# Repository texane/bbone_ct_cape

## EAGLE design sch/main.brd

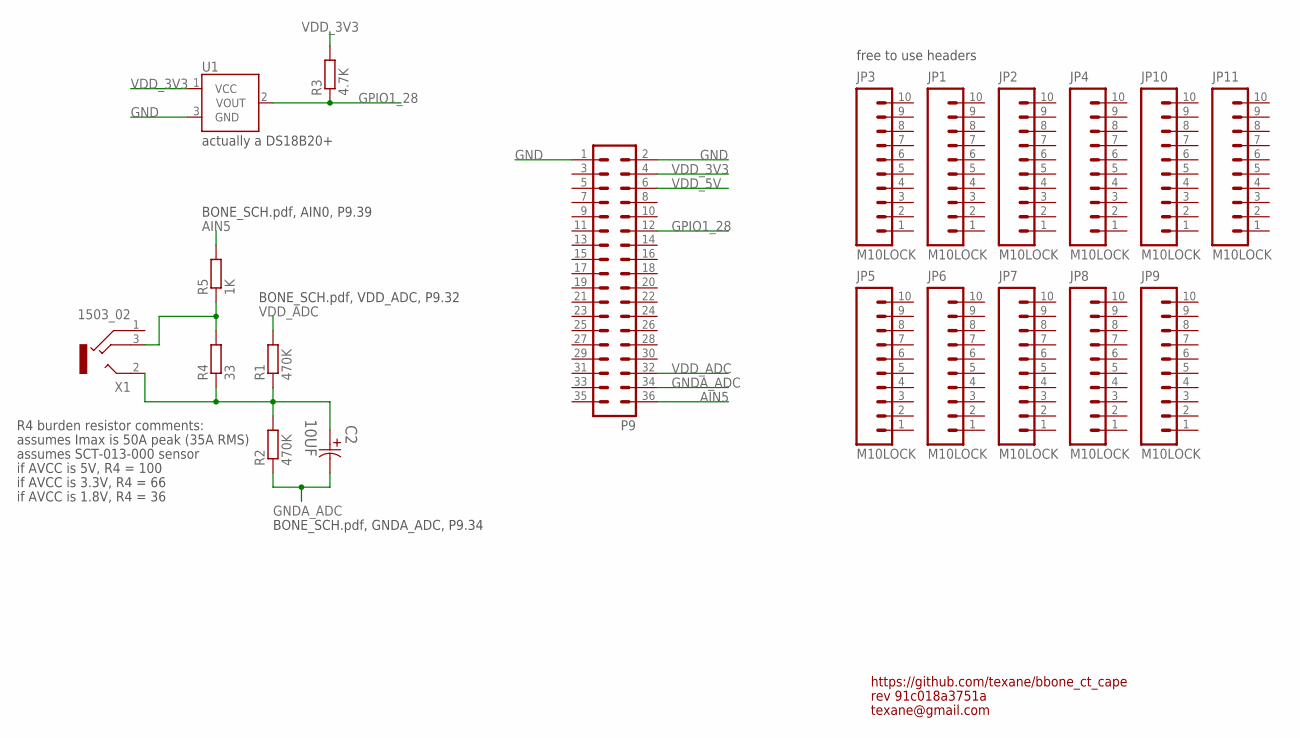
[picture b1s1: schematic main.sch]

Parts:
C2: 10UF; CAPAE530X610N
JP1, JP2, JP3, JP4, JP5, JP6, JP7, JP8, JP9, JP10, JP11: M10LOCK; 1X10_LOCK
P9: MA18-2
R1, R2: 470K; M1206
R3: 4.7K; M1206
R4: 33; M1206
R5: 1K; M1206
U1: TMP36TO-92-KIT; TO-92-KIT
X1: 1503_02

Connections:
AIN5: P9.36, R5.2
GND: P9.1, P9.2, U1.3 (GND)
GNDA_ADC: C2.2, P9.34, R2.1
GPIO1_28: P9.12, R3.1, U1.2 (VOUT)
unnamed: C2.1, R1.1, R2.2, R4.1, X1.2
unnamed: R4.2, R5.1, X1.3
VDD_3V3: P9.4, R3.2, U1.1 (VCC)
VDD_5V: P9.6
VDD_ADC: P9.32, R1.2

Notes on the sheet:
R4 burden resistor comments:
if AVCC is 5V, R4 = 100
if AVCC is 3.3V, R4 = 66
if AVCC is 1.8V, R4 = 36
assumes Imax is 50A peak (35A RMS)
assumes SCT-013-000 sensor
BONE_SCH.pdf, VDD_ADC, P9.32
BONE_SCH.pdf, GNDA_ADC, P9.34
BONE_SCH.pdf, AIN0, P9.39
actually a DS18B20+
free to use headers
texane@gmail.com
rev 91c018a3751a
https://github.com/texane/bbone_ct_cape

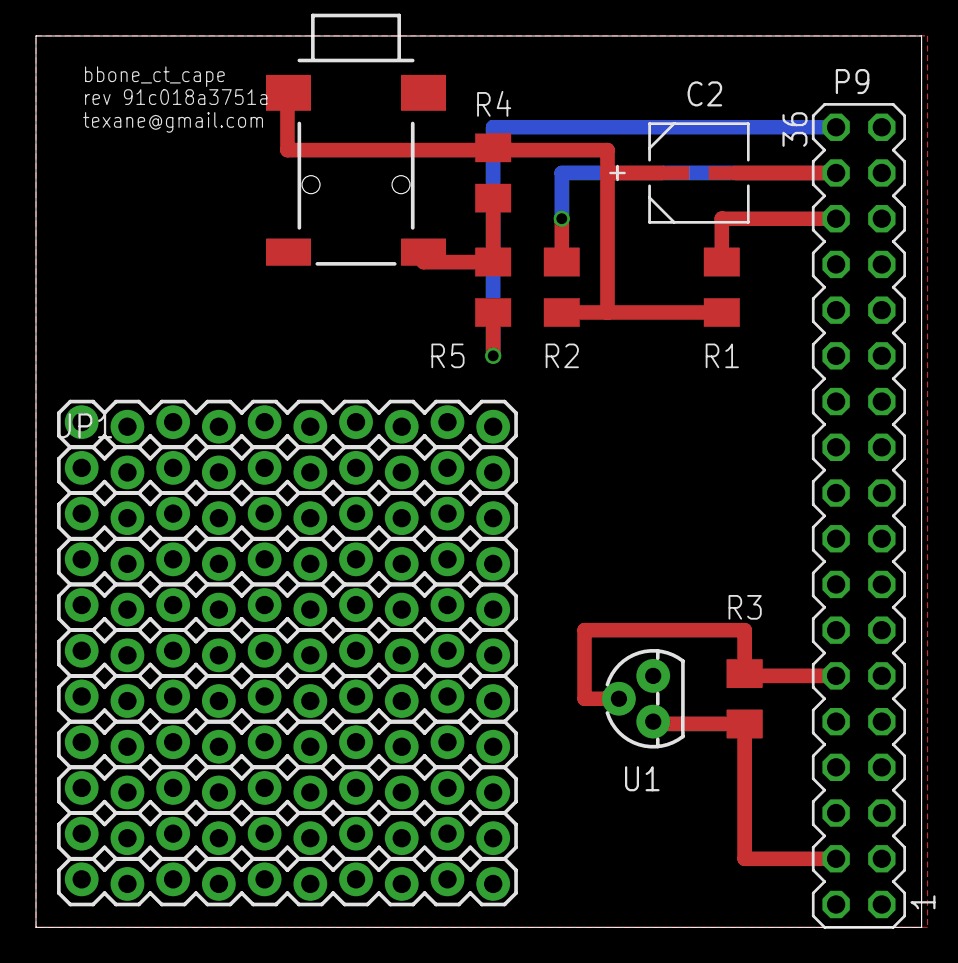
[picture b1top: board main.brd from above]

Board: 2 copper layers, 49.2 x 49.5 mm, 20 parts (0 on the bottom side), 8 nets.

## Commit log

2014-10-14 [ add ] notes
2014-10-15 [ add ] sch
2014-10-15 [ update ] doc/notes
2014-10-15 [ add ] ds/DS18B20
2014-10-15 [ add ] sch/third/adafruit.lib
2014-10-15 [ update, add ] board
2014-10-15 [ update ] schematics
2014-10-15 [ update ] notes
2014-10-15 [ update ] schematics revision
2014-10-15 [ update ] bom
2014-10-15 [ add ] sch/main.pdf
2014-10-15 [ add ] sch/gerber/main_91c018a3751a.zip
2014-10-15 [ update ] main.brd
2014-10-15 [ add ] ds
2014-10-15 [ update ] sch
2014-11-04 [ add ] doc/xxx_certifs

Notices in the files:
parts and their libraries:
SparkFun: Licensing: CC v3.0 Share-Alike You are welcome to use this library for commercial purposes.
